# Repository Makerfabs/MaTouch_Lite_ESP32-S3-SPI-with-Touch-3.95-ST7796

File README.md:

# MaTouch_Lite_ESP32-S3-SPI-with-Touch-3.95-ST7796

## Introduction

The MaTouch Lite 3.95 adopts an SPI screen driven by ST7796 chip with a resolution of 480×320, matched with NS2009 resistive touch screen. It is equipped with ESP32-S3 main controller, built-in 16M Flash and 8M PSRAM. Adopting SPI display design, plenty of reserved GPIOs are available for secondary development via GPIO expansion interface. It also comes with SD card interface and USB native/USB2UART port.

Product Link: [MaTouch_Lite_ESP32-S3-SPI-with-Touch-3.95-ST7796](https://www.makerfabs.com/matouch-lite-esp32-s3-spi-resistive-touch-3-95-st7796.html)

Wiki Link:  [MaTouch_Lite_ESP32-S3-SPI-with-Touch-3.95-ST7796](https://wiki.makerfabs.com/MaTouch%20Lite%20ESP32_S3%20SPI%20with%20Touch%203.95%20ST7796.html)

Example：[LVGL_Touch](https://github.com/Makerfabs/MaTouch_Lite_ESP32-S3-SPI-with-Touch-3.95-ST7796#lvgl_touch)

## Feature

- Controller: ESP32-S3 controller 16M flash, 8M PSRAM
- Display: 3.95", 480x320 resolution , driver ST7796, SPI interface
- Touch Panel: Resistive, NS2009
- USB: 1 * USB_native, 1 * USB-to-UART
- USB-UART Driver: CH340K
- Power Supply: USB Type-C 5.0V(4.0V~5.25V); 3.7V Lipo battery
- Expansion interface: 2*JST1.25mm-4P GPIO, with cable included
- MicroSD Card Slot
- LCD Backlight control: Yes
- Arduino support: Yes
- LVGL support: Yes
- Operation temperature: -40℃ to +85℃

## Usage in Arduino IDE

- Install the Arduino IDE V1.8.19/V2.3.6
If you haven’t installed the ESP32 Board SDK yet, follow the steps in this [guide](https://wiki.makerfabs.com/Installing_ESP32_Add_on_in_Arduino_IDE.html) to get started quickly.

For the ESP32-S3 Development board version, we recommend using versions that have been verified, such as 2.0.16， which is more stable, and less prone to errors.

Note: Different computers may have different port numbers when connecting to a development board. Please select the correct port number based on the development board you are connecting to.

Please download the relevant driver libraries before using these demos.

1.Install Adafruit_BusIO v1.17.4

2.Install Adafruit_SGP30_Sensor v2.0.3

3.Install Adafruit_SHT31_Library v2.2.2

## Example

### LVGL_Touch

This demonstration showcases the integrated application of display and touch. The screen initially shows an image with data such as temperature, humidity, CO2, TVOC,and touch point coordinates. If the screen is not touched within 10 seconds, it will automatically turn off. After the screen turns off, clicking on it will make it bright again and display the data.

- First, connect the Mabee module to the ESP32-S3 module correctly, as shown in the figure.

- Download the library from [github](https://github.com/Makerfabs/MaTouch_Lite_ESP32-S3-SPI-with-Touch-3.95-ST7796/tree/main/example/LVGL_Touch/libraries)

Once the download is complete, copy these libraries into the Arduino library.

- The default is usually in the "C:\Users\Your username\Documents\Arduino\libraries"

**Note: If the UI, LVGL or TFT_eSPI library already exists in your Arduino libraries folder, please delete them first, then install the new version of the UI, LVGL or TFT_eSPI library.**

- Open the [LVGL_Touch](https://github.com/Makerfabs/MaTouch_Lite_ESP32-S3-SPI-with-Touch-3.95-ST7796/blob/main/example/LVGL_Touch/ui/ui.ino) by Arduino.

Connect the board to the computer using a Type-C USB data cable and via USB-TTL, and select the development board "ESP32S3 Dev Module" and the port.

- Select "Tools > board:"xxx" > ESP32 > ESP32S3 Dev Module".
- Select "Tools > Port",Select the port number of the board.
- Select Flash Size is 16MB(128MB), Partition Scheme is 16M Flash (3MB APP/9.9MB FATFS), PSRAM is OPI PSRAM.

- Click the Upload button in the Arduino IDE and wait a few times while the code compiles and uploads to your board.

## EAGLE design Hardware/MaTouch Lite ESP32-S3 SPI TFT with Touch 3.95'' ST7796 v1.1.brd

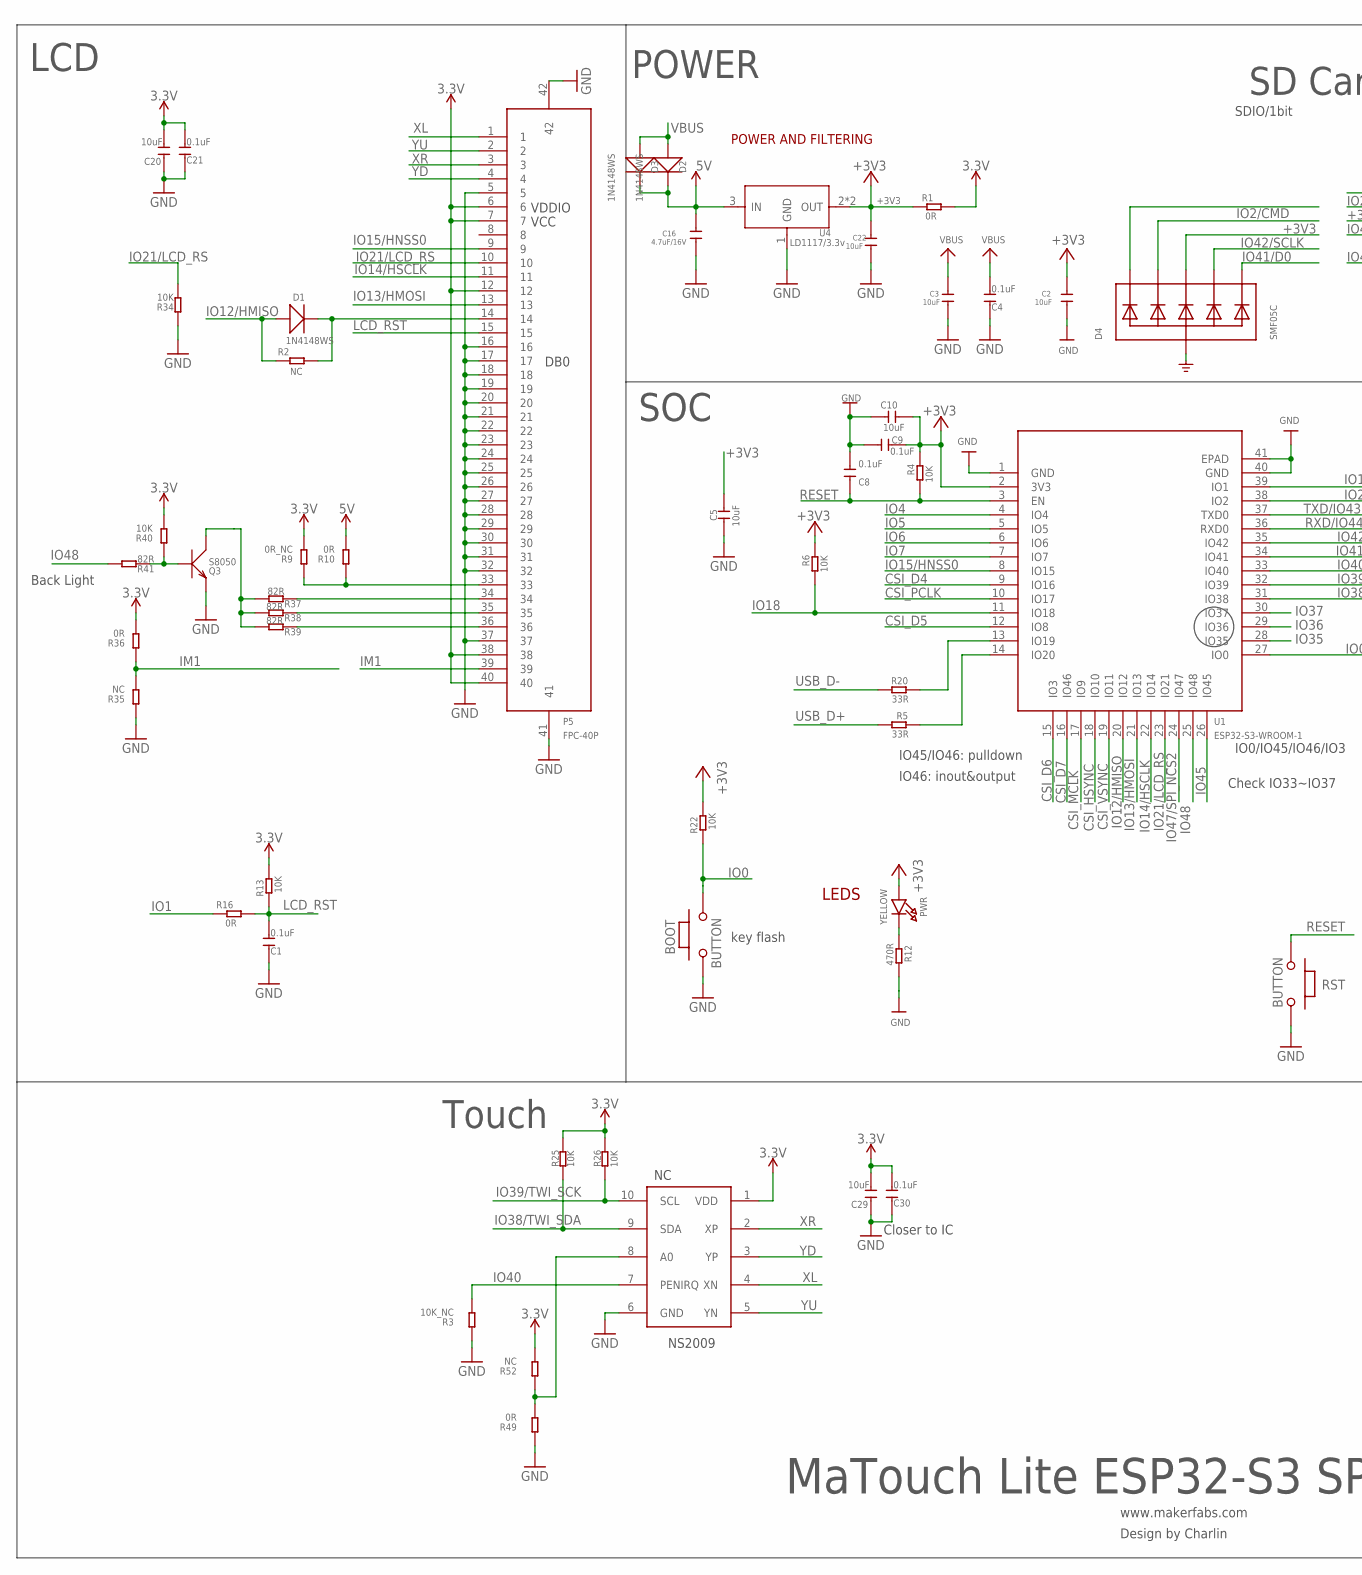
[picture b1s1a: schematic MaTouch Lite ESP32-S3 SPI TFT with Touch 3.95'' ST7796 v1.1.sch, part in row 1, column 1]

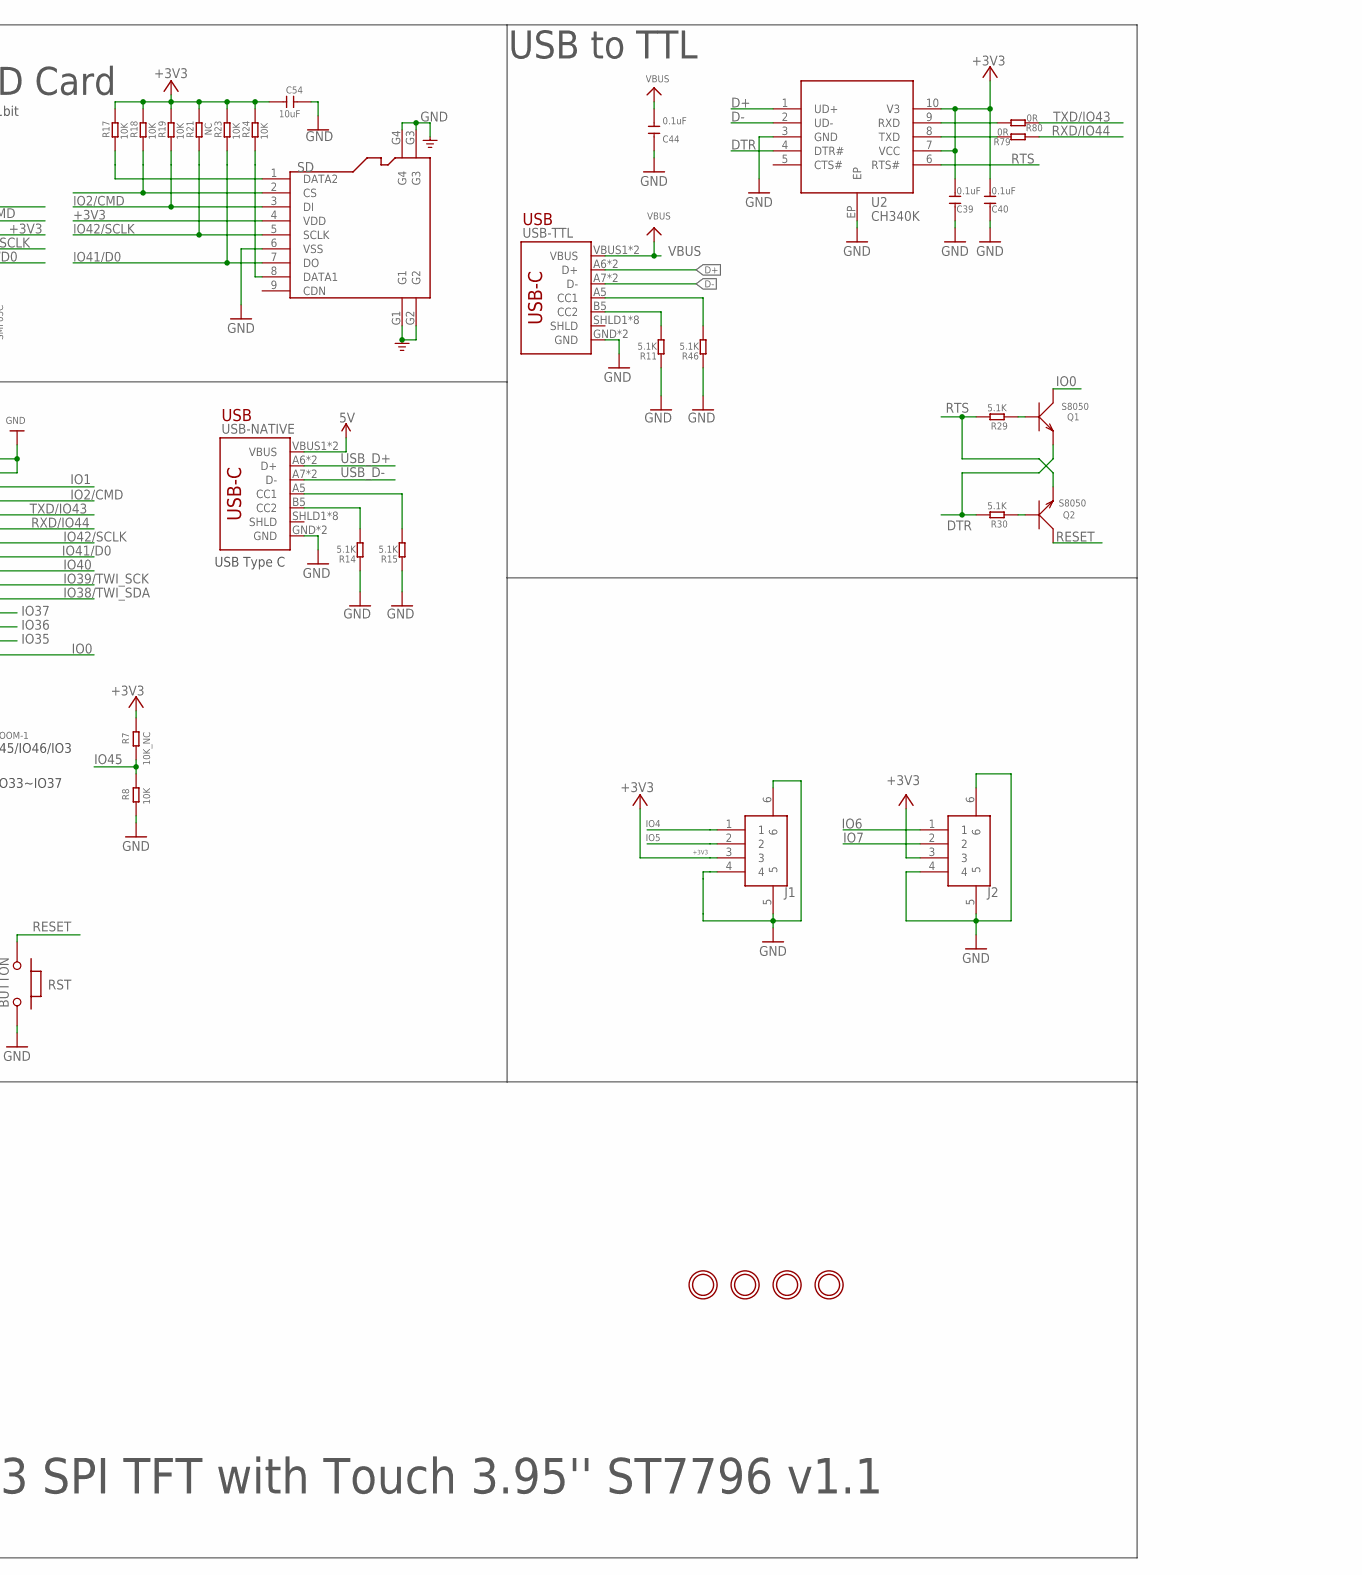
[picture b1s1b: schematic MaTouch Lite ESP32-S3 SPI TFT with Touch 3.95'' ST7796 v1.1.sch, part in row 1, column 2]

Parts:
BOOT: BUTTON; 157SW
C1, C4, C8, C9, C21, C30, C39, C40, C44: 0.1uF; DISCRETE_C0603
C2, C3, C22: 10uF; 0603
C5, C10, C20, C29, C54: 10uF; DISCRETE_C0603
C16: 4.7uF/16V; 0603
D1, D2, D3: 1N4148WS; SOD323
D4: SMF05C; SOT363
H1, H2, H3, H4: MICROBUILDER_MOUNTINGHOLE3.0THIN; MICROBUILDER_MOUNTINGHOLE_3.0_PLATEDTHIN
J1, J2: CON4-1.25P-SMD; SMD4-125P-1000L525W350H
P5: FPC-40P; SMD42-50P-2560L490W
PWR: YELLOW; CHIPLED_0805_NOOUTLINE
Q1, Q2, Q3: S8050; SOT23
R1, R16, R79, R80: 0R; R0603
R2, R21: NC; R0603
R3: 10K_NC; DISCRETE_R0603
R4, R6, R8, R13, R17, R18, R19, R22, R23, R24, R25, R26: 10K; R0603
R5, R20: 33R; R0603
R7: 10K_NC; R0603
R9: 0R_NC; DISCRETE_R0603
R10, R36, R49: 0R; DISCRETE_R0603
R11, R14, R15, R46: 5.1K; DISCRETE_R0603
R12: 470R; R0603
R29, R30: 5.1K; R0603
R34, R40: 10K; DISCRETE_R0603
R35, R52: NC; DISCRETE_R0603
R37, R38, R39, R41: 82R; DISCRETE_R0603
RST: BUTTON; 157SW
SD: HOLDER-MICROSD-9P; 9P-SMD-W/-RING
U1: ESP32-S3-WROOM-1
U2: CH340K; ESOP-10-EP-150MIL
U4: LD1117/3.3v; SOT89
U8: NS2009; MSOP10
USB-NATIVE: USB_C5; USB-C-16P-5
USB-TTL: USB_C5; USB-C-16P-5

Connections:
5V: C16.1, D2.-, D3.-, R10.2, U4.3 (IN), USB-NATIVE.VBUS1 (VBUS), USB-NATIVE.VBUS2 (VBUS)
+3V3: C2.1, C5.1, C9.1, C10.1, C20.2, C21.2, C22.1, C29.2, C30.2, C39.2, C40.2, C54.2, D4.4 (C3), J1.3, J2.3, P5.6, P5.7, P5.12, P5.38, P5.40, PWR.A, R1.1, R1.2, R4.2, R6.2, R7.2, R9.2, R13.2, R17.2, R18.2, R19.2, R21.2, R22.2, R23.2, R24.2, R25.2, R26.2, R36.2, R40.2, R52.2, SD.4 (VDD), U1.2 (3V3), U2.7 (VCC), U2.10 (V3), U4.2 (OUT), U4.4 (OUT), U8.1 (VDD)
CSI_D4: U1.9 (IO16)
CSI_D5: U1.12 (IO8)
CSI_D6: U1.15 (IO3)
CSI_D7: U1.16 (IO46)
CSI_HSYNC: U1.18 (IO10)
CSI_MCLK: U1.17 (IO9)
CSI_PCLK: U1.10 (IO17)
CSI_VSYNC: U1.19 (IO11)
D+: U2.1 (UD+), USB-TTL.A6 (D+), USB-TTL.B6 (D+)
D-: U2.2 (UD-), USB-TTL.A7 (D-), USB-TTL.B7 (D-)
DTR: Q1.2 (E), R30.2, U2.4 (DTR#)
GND: BOOT.1, C1.1, C2.2, C3.2, C4.1, C5.2, C8.2, C9.2, C10.2, C16.2, C20.1, C21.1, C22.2, C29.1, C30.1, C39.1, C40.1, C44.1, C54.1, D4.2 (A), J1.4, J1.5, J1.6, J2.4, J2.5, J2.6, P5.5, P5.16, P5.17, P5.18, P5.19, P5.20, P5.21, P5.22, P5.23, P5.24, P5.25, P5.26, P5.27, P5.28, P5.29, P5.30, P5.31, P5.32, P5.37, P5.41, P5.42, Q3.2 (E), R3.1, R8.1, R11.1, R12.2, R14.1, R15.1, R34.1, R35.1, R46.1, R49.1, RST.1, SD.6 (VSS), SD.G1, SD.G2, SD.G3, SD.G4, U1.1 (GND), U1.40 (GND), U1.41 (EPAD), U2.3 (GND), U2.EP, U4.1 (GND), U8.6 (GND), USB-NATIVE.GND, USB-NATIVE.GND2 (GND), USB-TTL.GND, USB-TTL.GND2 (GND)
IM1: P5.39, R35.2, R36.1
IO0: BOOT.2, Q1.3 (C), R22.1, U1.27 (IO0)
IO1: R16.1, U1.39 (IO1)
IO1/CS: D4.1 (C1), R18.1, SD.2 (CS)
IO2/CMD: D4.3 (C2), R19.1, SD.3 (DI), U1.38 (IO2)
IO4: J1.1, U1.4 (IO4)
IO5: J1.2, U1.5 (IO5)
IO6: J2.1, U1.6 (IO6)
IO7: J2.2, U1.7 (IO7)
IO12/HMISO: D1.+, R2.1, U1.20 (IO12)
IO13/HMOSI: P5.13, U1.21 (IO13)
IO14/HSCLK: P5.11, U1.22 (IO14)
IO15/HNSS0: P5.9, U1.8 (IO15)
IO18: R6.1, U1.11 (IO18)
IO21/LCD_RS: P5.10, R34.2, U1.23 (IO21)
IO35: U1.28 (IO35)
IO36: U1.29 (IO36)
IO37: U1.30 (IO37)
IO38/TWI_SDA: R25.1, U1.31 (IO38), U8.9 (SDA)
IO39/TWI_SCK: R26.1, U1.32 (IO39), U8.10 (SCL)
IO40: R3.2, U1.33 (IO40), U8.7 (PENIRQ)
IO41/D0: D4.6 (C5), R23.1, SD.7 (DO), U1.34 (IO41)
IO42/SCLK: D4.5 (C4), R21.1, SD.5 (SCLK), U1.35 (IO42)
IO45: R7.1, R8.2, U1.26 (IO45)
IO47/SPI_NCS2: U1.24 (IO47)
IO48: R41.2, U1.25 (IO48)
LCD_RST: C1.2, P5.15, R13.1, R16.2
unnamed: R46.2, USB-TTL.A5 (CC1)
unnamed: D1.-, P5.14, R2.2
unnamed: Q2.1 (B), R30.1
unnamed: PWR.C, R12.1
unnamed: Q1.1 (B), R29.1
unnamed: R15.2, USB-NATIVE.A5 (CC1)
unnamed: R20.2, U1.13 (IO19)
unnamed: R5.2, U1.14 (IO20)
unnamed: R14.2, USB-NATIVE.B5 (CC2)
unnamed: R11.2, USB-TTL.B5 (CC2)
unnamed: P5.34, R37.1
unnamed: P5.35, R38.1
unnamed: P5.36, R39.1
unnamed: Q3.1 (B), R40.1, R41.1
unnamed: Q3.3 (C), R37.2, R38.2, R39.2
unnamed: R49.2, R52.1, U8.8 (A0)
unnamed: P5.33, R9.1, R10.1
unnamed: R80.2, U2.9 (RXD)
unnamed: R79.2, U2.8 (TXD)
unnamed: R17.1, SD.1 (DATA2)
unnamed: R24.1, SD.8 (DATA1)
RESET: C8.1, Q2.3 (C), R4.1, RST.2, U1.3 (EN)
RTS: Q2.2 (E), R29.2, U2.6 (RTS#)
RXD/IO44: R79.1, U1.36 (RXD0)
TXD/IO43: R80.1, U1.37 (TXD0)
USB_D+: R5.1, USB-NATIVE.A6 (D+), USB-NATIVE.B6 (D+)
USB_D-: R20.1, USB-NATIVE.A7 (D-), USB-NATIVE.B7 (D-)
VBUS: C3.1, C4.2, C44.2, D2.+, D3.+, USB-TTL.VBUS1 (VBUS), USB-TTL.VBUS2 (VBUS)
XL: P5.1, U8.4 (XN)
XR: P5.3, U8.2 (XP)
YD: P5.4, U8.3 (YP)
YU: P5.2, U8.5 (YN)

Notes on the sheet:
www.makerfabs.com
Design by Charlin
LEDS
POWER AND FILTERING
key flash
MaTouch Lite ESP32-S3 SPI TFT with Touch 3.95'' ST7796 v1.1
POWER
USB to TTL
SD Card
NS2009
Closer to IC
Back Light
IO45/IO46: pulldown
IO46: inout&output
USB
USB Type C
IO0/IO45/IO46/IO3
Check IO33~IO37
LCD
SOC
Touch
VDDIO
VCC
DB0
SDIO/1bit

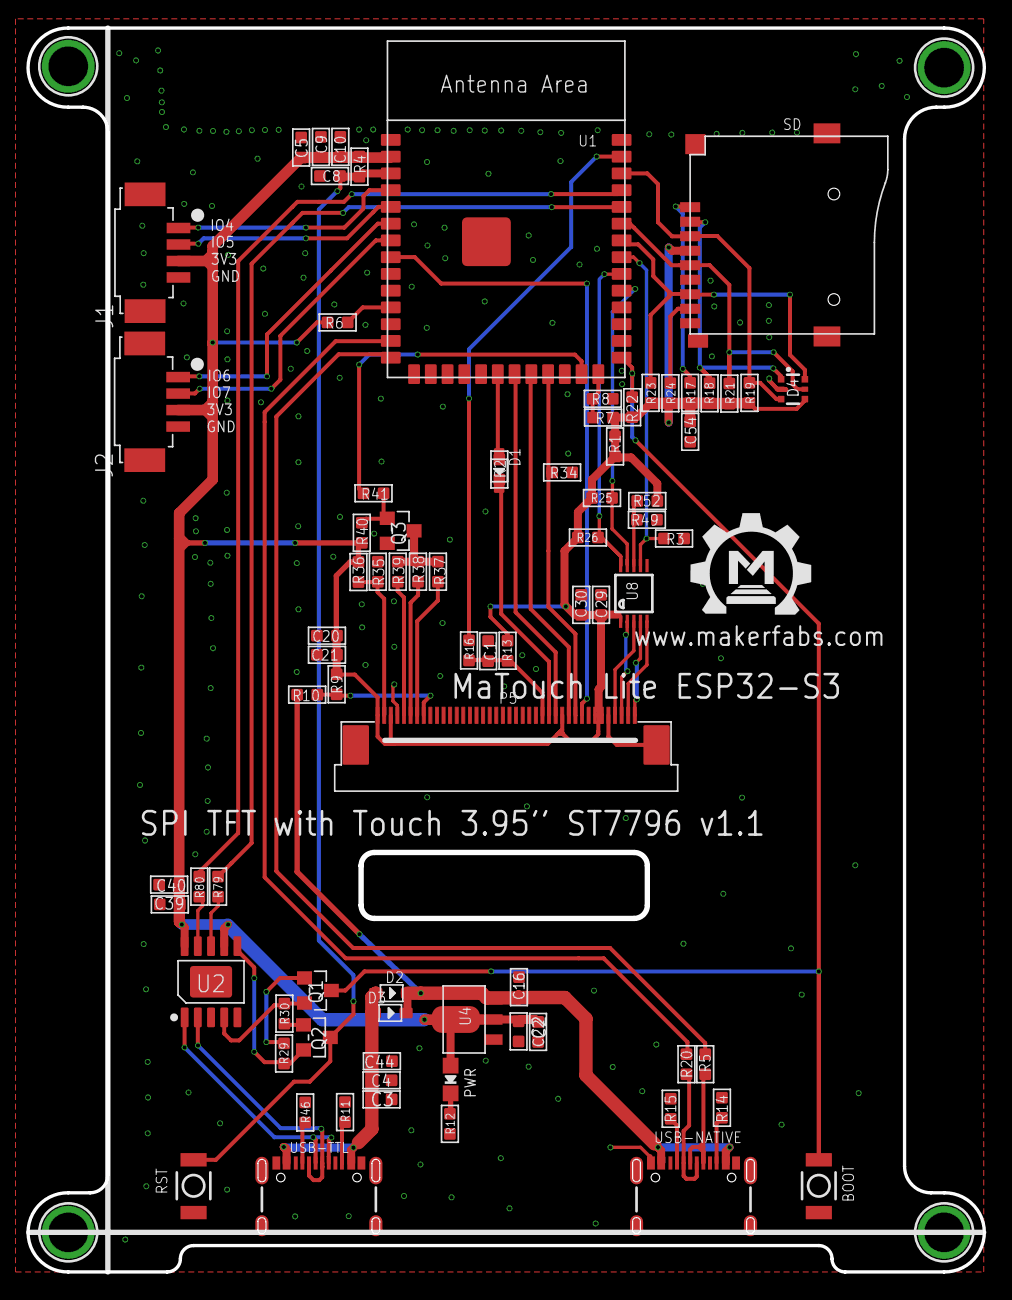
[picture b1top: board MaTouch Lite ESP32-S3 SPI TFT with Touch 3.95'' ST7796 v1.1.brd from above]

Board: 2 copper layers, 72.5 x 94.3 mm, 84 parts (0 on the bottom side), 61 nets.

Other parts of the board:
U$1: MAKERFABS_0.3

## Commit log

2026-05-14 Add code
2026-05-14 Add Schematic Diagram
2026-05-14 Add datasheet
2026-05-20 Add hardware
2026-05-21 Add README

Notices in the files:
parts and their libraries:
microbuilder: This work is placed in the public domain, and may be freely used for commercial and non-commercial work with the following conditions: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
SparkFun-PowerSymbols: Licensing: Creative Commons ShareAlike 4.0 International - https://creativecommons.org/licenses/by-sa/4.0
